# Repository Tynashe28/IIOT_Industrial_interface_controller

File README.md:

# IIOT_Industrial_interface_controller

## Introduction

Remote monitoring and controlling systems are designed to collect data about the operations of any given unit or transmit information to the unit to transform its behavior via the cloud. You benefit from leveraging the Industrial Internet of Things (IIoT). OEMs, end-users and systems integrators have already seen the benefits of implementing a remote monitoring system that lead to increased productivity, reduced production costs and enhanced user experience.

Drakula is an Industrial Internet of Things gateway controller which seeks to connect manufacturing processes to the internet with zero effort and unleash the usefulness and power of technology in this field at zero cost. This controller makes it easy for industries to leverage trending and growing technologies like machine learning, IoT, blockchain, web backend services into their day to day operations. The beauty about Drakula is that it integrates on top of existing architectures and virtually no change can be made to existing setups to accommodate it.  

### Core Values
•	Zero Effort\
•	Zero Cost\
•	Interactive\
•	Value Addition

## How it works

From a high level, the Drakula connects to the plant process and it accesses field parameters about a manufacturing process. It can also be granted privileges to write data to alter the behavior of processes within the plant. Drakula relays this information to a cloud platform via an API where data analytics can also be done.

The ability of this controller to access field parameters and make them accessible over the web opens vast opportunities for manufacturing processes.

•	Information can be relayed to mobile phones, desktop or smart watches.\
•	Interacting with manufacturing processes just becomes easy through our day to day devices.\
•	Implementing sophisticated algorithms which can never be done on PLCs’ in the cloud to improve processes.\
•	Ability to build intuitive and interactive SCADA dashboards which can never be offered by PLCs\

### Example Use Case
Let’s take a practical example of defects after “beer” filling 😃. We can make use of the real time number defects of the filler to come up with the REAL-TIME STATE OF THE MACHINE. We can also produce predictions of the number of defects after some time “x” which can open doors to generate a predictive maintenance schedule for the machine.

## Motivation in Building This Product
•	All most every software and hardware used in industry is highly proprietary to the company that provides that piece of hardware or software. These services come at a hefty amount which leaves us with no room to be innovative with their products as most companies cannot afford. Building a product for less than USD50 to counter this problem should be enough to motivate engineers to start get their hands dirty with these technologies.

•	A PLC is very excellent at the job it was made for. Problems start when you try to perform computations which require more memory or power from the system like training a Machine Learning model. It even gets more complicated than rocket science when you try to perform a simple HTTP request to the internet from a PLC. One of the core values of Drakula is Zero Effort, you don’t have to worry about the low-level implementations of establishing internet connection. Offering this abstraction layer makes engineers focus more on the task to be achieved rather than implementation details.

•	The way reports are generated in industry today is just primitive, data is organized either at end of a shift or day, meaning we don’t get to visualize real-time plant performances. Manufacturing should be also powered by Interactive and Real-time dashboards.

•	A lot of technologies are being developed over the Internet which can be harnessed in operations and processes to increase manufacturing efficiencies and business profitability

## Considerations made into the design

•	Interoperable – Drakula is compatible with almost every industrial setup. It runs in parallel with existing architectures. Taking advantage that every industrial PLC has a communication channel which can be used as desired with no restriction, forms the point of connectivity for the devices.

•	Robust – Controller components to handle high temperatures, voltage fluctuations, electromagnetic interference and induction.

•	Reliability – Additional components to a system has a consequence of reducing the overall reliability of a process. This controller has been designed in a way that it runs in parallel with the overall plant process in a bid to make the controller have zero effect on the plant process in case of a failure. 

•	Hardware Abstraction – Developers implementing this board should have easy ability to integrate this controller. This is made possible by providing ready-to-use drivers which do all low-level heavy lifting.

•	Security & Industrial Standards – The security of a system is as good as its weakest point. This controller aims to keep the integrity of the data that it is processing. Every web request is done via Web-Sockets over HTTPS. Every component used on the controller is accredited to be industrial grade.

•	Overall System Efficiency – Drakula’s main CPU is a high-performance processor which runs a real-time operating system which manages all tasks and this makes sure the system is seamless and operates without any lag.

•	Maintainability – Ability of controller to connect to Wi-Fi access points gives it the ability to be maintained over the air, incase of software updates and troubleshooting. Incase of a hardware fault, the device can be disconnected from the system without affecting the main production processes.

•	Cost – The total cost of producing 1 controller excluding Labour and Tooling is capped at maximum of USD50.00 (PCB Manufacturing, Components and Assembly).

## Why Implement Drakula

### Improve Productivity
Overall Equipment Effectiveness, or OEE, is a productivity measurement that combines downtime, production rate and quality. OEE has long been the gold standard for increasing productivity, but the Industrial Internet of Things has made OEE much more affordable and easier to implement than ever before. 

### Information at Your Fingertips
Line operators, maintenance crews and production supervisors all have a significant impact on the productivity of the manufacturing lines. Without information readily available, it is more difficult to address the highest priority production issues within a timely manner.

### Data Reliability
It’s very common to see people using clipboards to copy data from gauges, operator interface screens or field sensors. Automated data collection is more efficient, more reliable and more consistent than manual data collection. The IIoT can provide seamless data flow starting at the device level and pushing the data directly to mobile devices, enterprise level software or other reporting systems.

### Reduce Downtime
Emails, push notifications and text alerts can provide immediate downtime alerts allowing you to address the issue as quickly as possible.  Root cause analysis allows you to diagnose the specific cause of a downtime event, and downtime analytics allow you to evaluate the true cost of each type of failure.  A remote monitoring solution is an easy and cost-effective way to incorporate all of these techniques to increase the reliability of your equipment.

### Predictive Maintenance
Predictive maintenance techniques can be used to monitor and analyze vibration, motor current, or temperature patterns and identify potential problems before they cause a shutdown. This can also reduce maintenance costs because maintenance can be performed when it is actually needed rather than simply scheduled.

### Intuitive Dashboards
Your car’s dashboard can tell you the remaining oil life, miles to empty, temperature, and more. Manufacturing lines need much more maintenance than a car, but required maintenance is usually not available from the equipment. User friendly dashboards on mobile and desktop apps also provide quick and easy way to visualize the whole plant.

## General System Architecture

### Main-Features
•	Supports all Ethernet communications (Modbus, Profinet, TCP etc.)\
•	Supports Modbus over RS-485\
•	Wi-Fi connectivity (Supports WebSocket connection)\
•	Bi-Directional Communication\
•	Asynchronous and Non-Blocking routines\
•	3 logical Processing Cores

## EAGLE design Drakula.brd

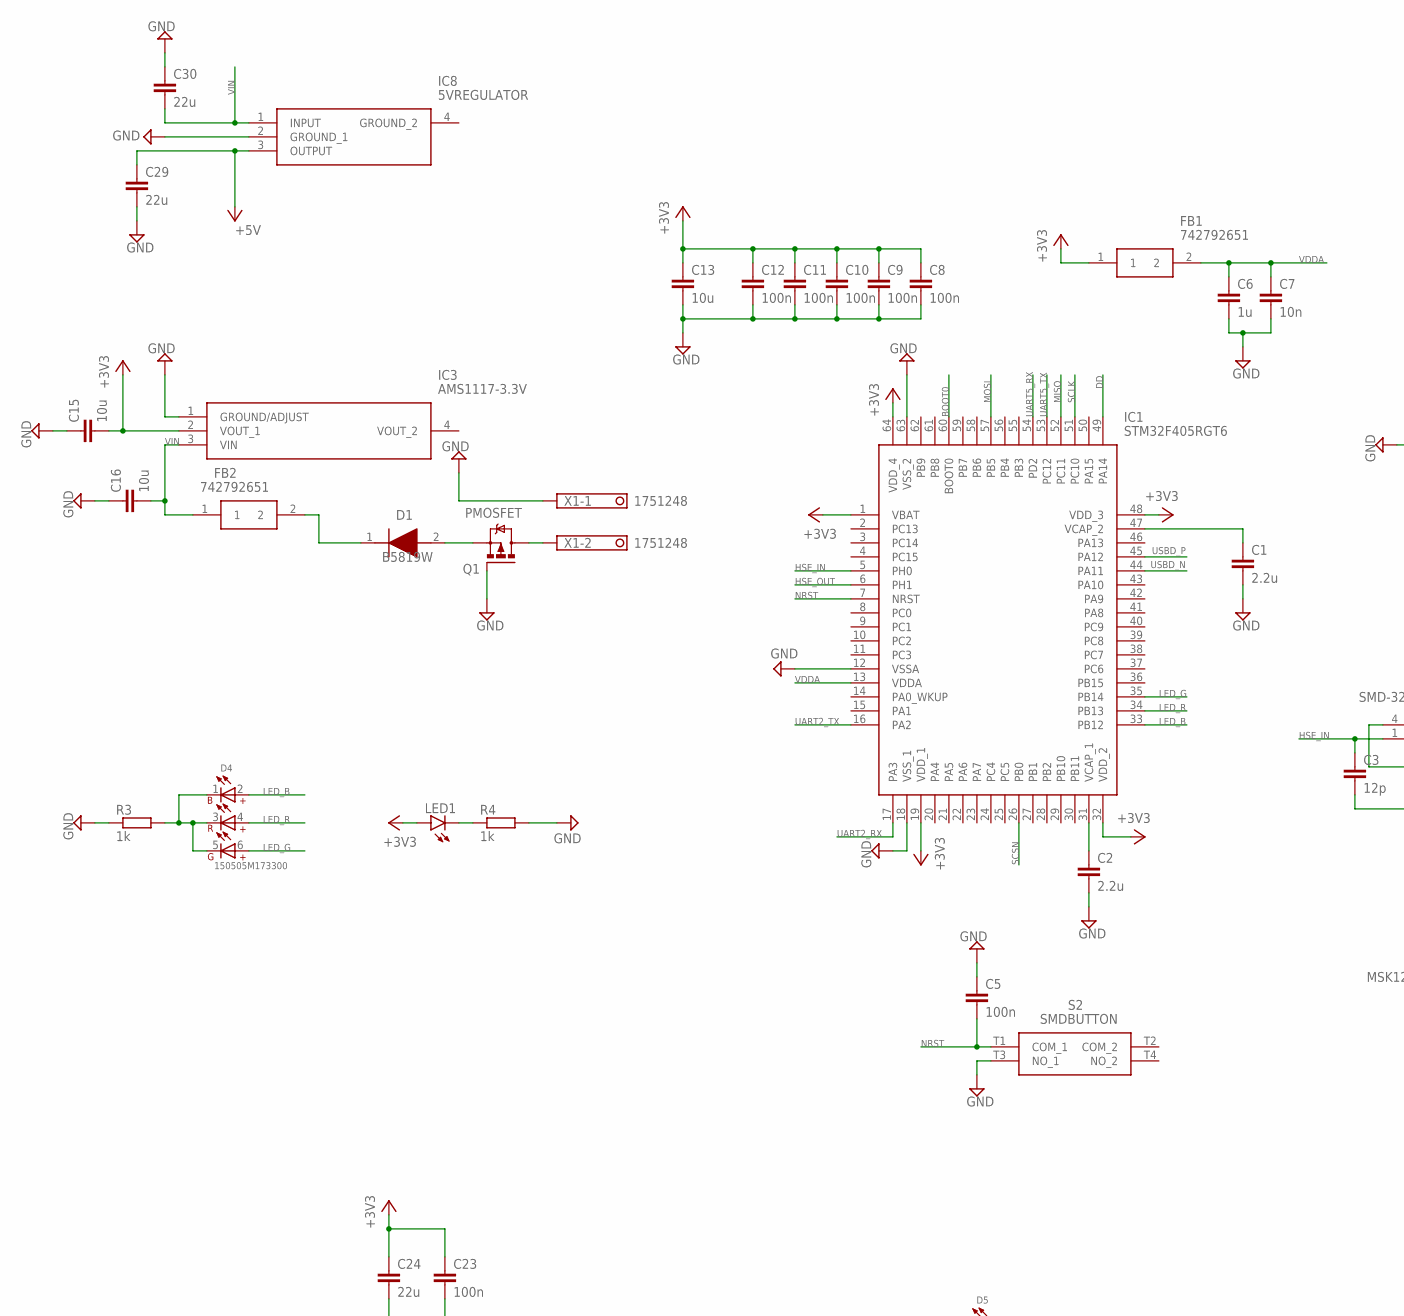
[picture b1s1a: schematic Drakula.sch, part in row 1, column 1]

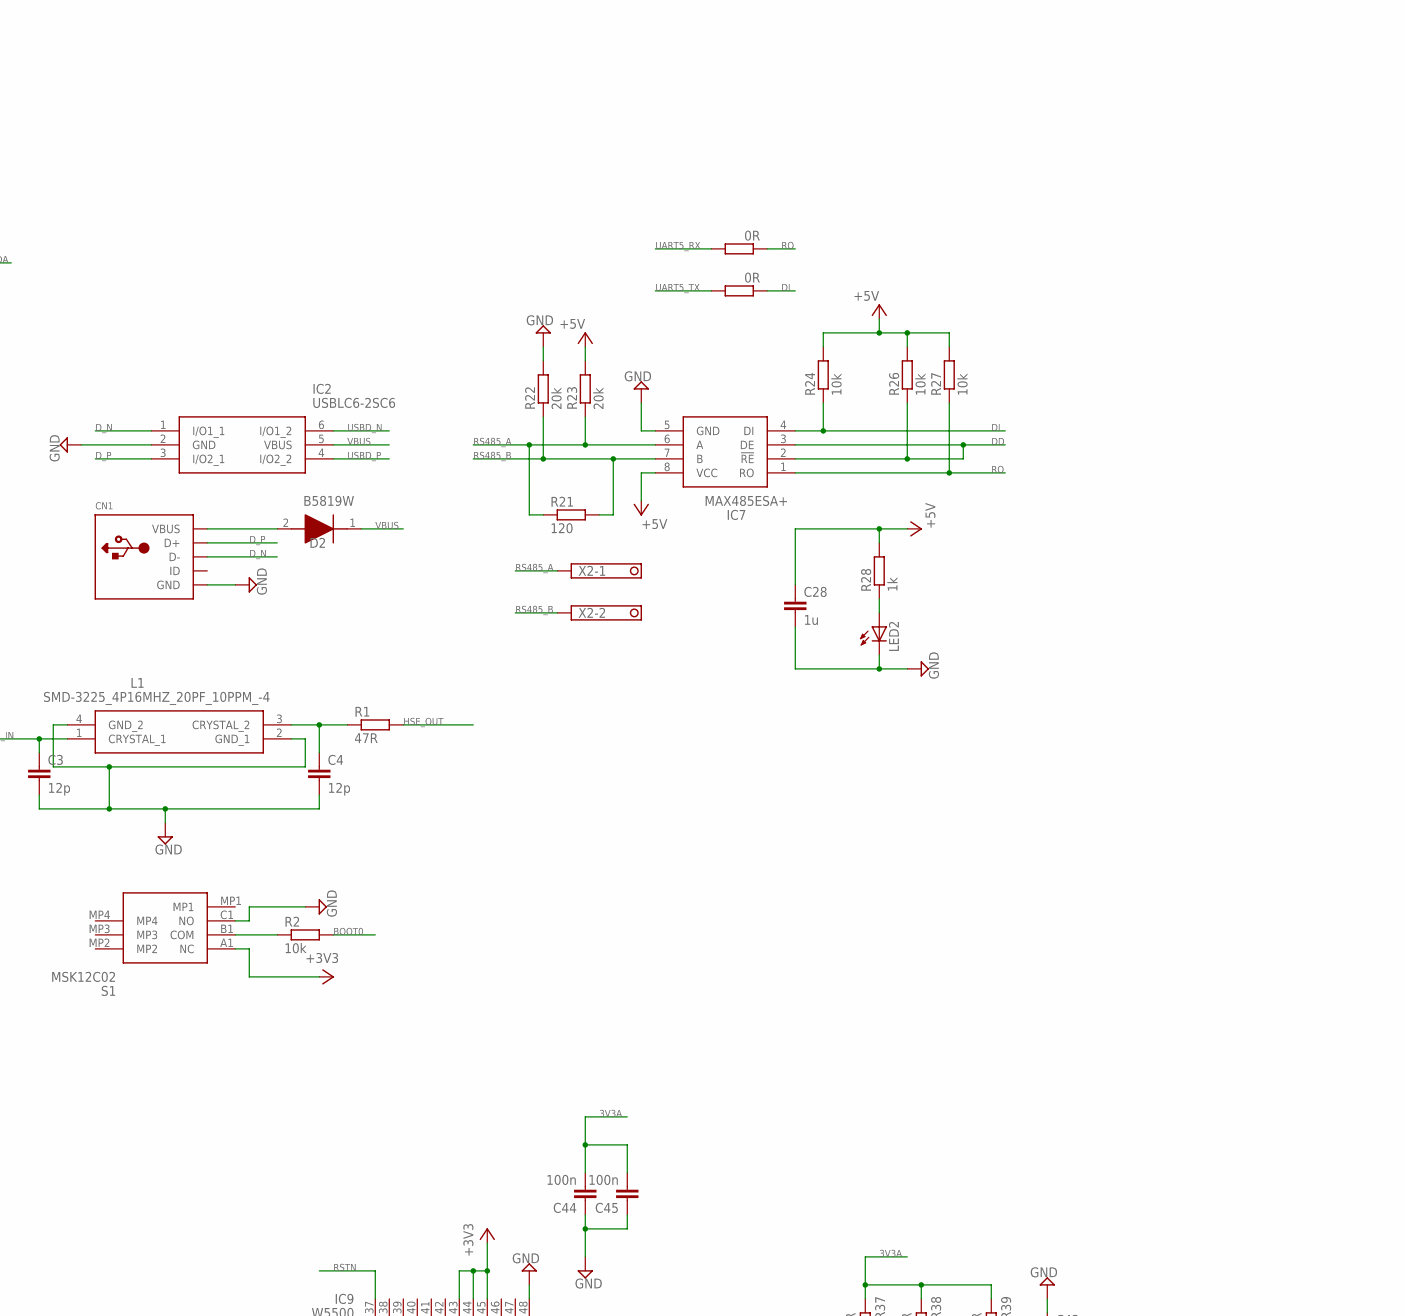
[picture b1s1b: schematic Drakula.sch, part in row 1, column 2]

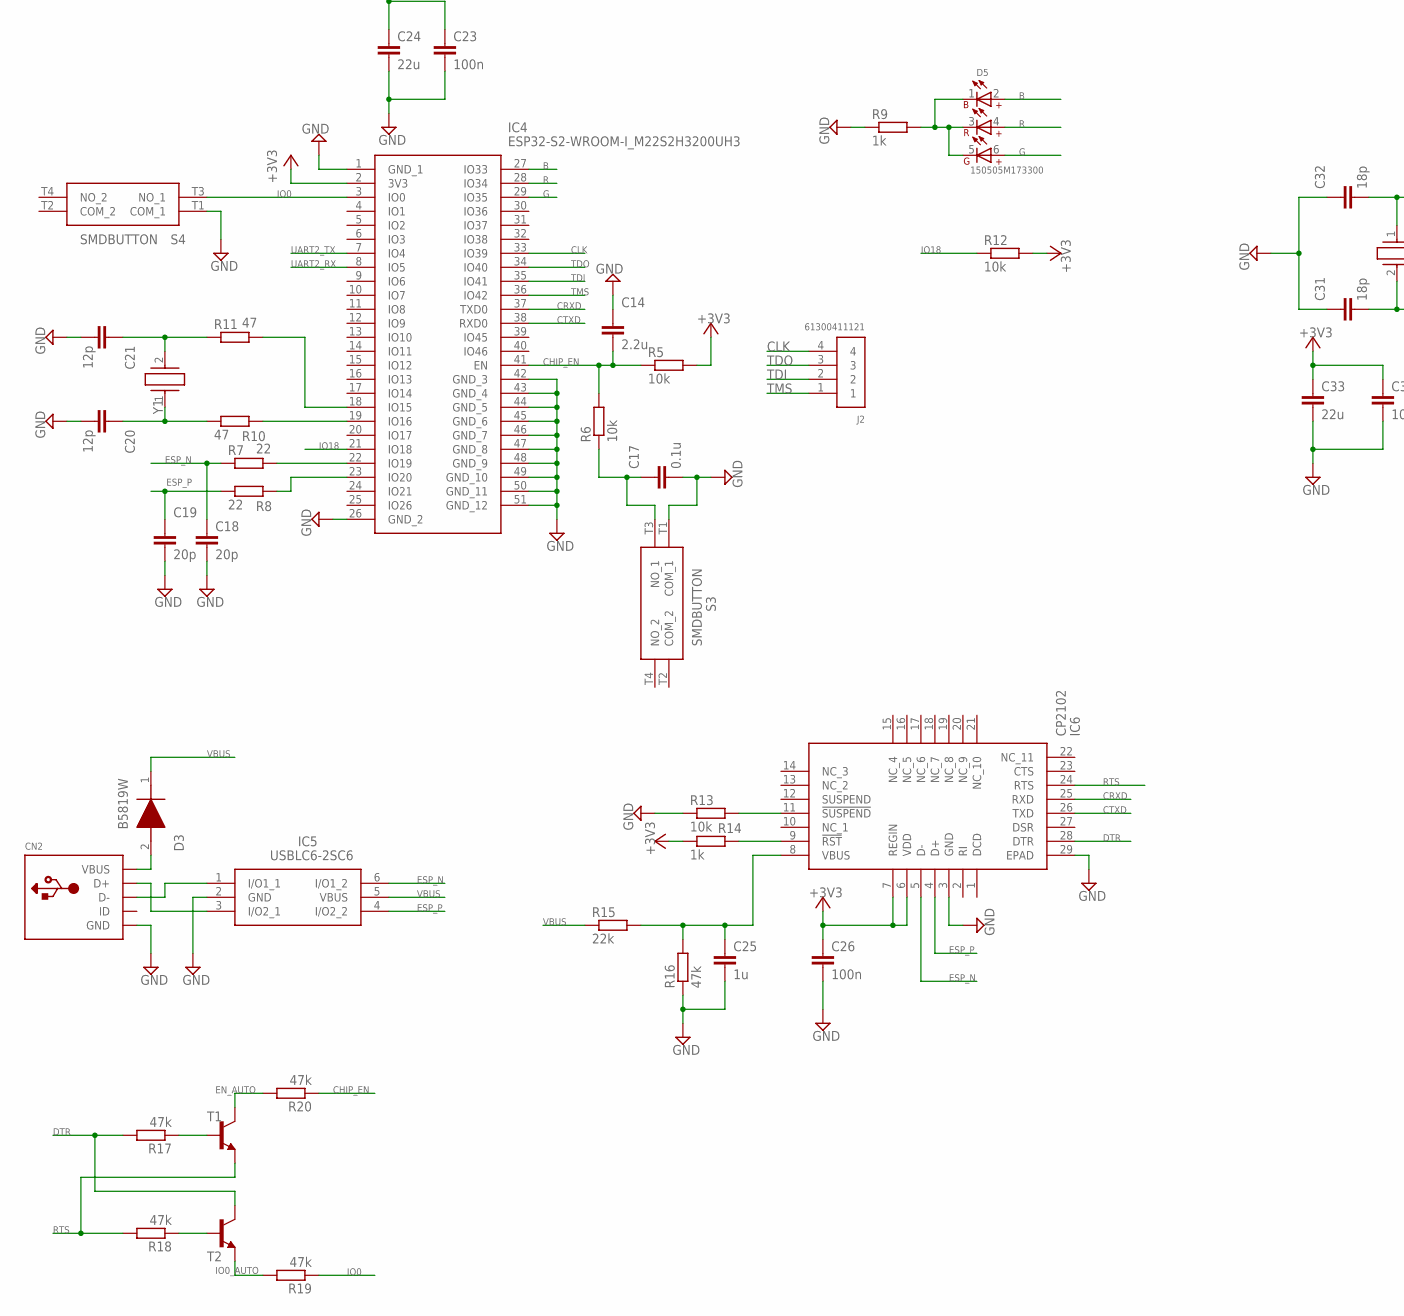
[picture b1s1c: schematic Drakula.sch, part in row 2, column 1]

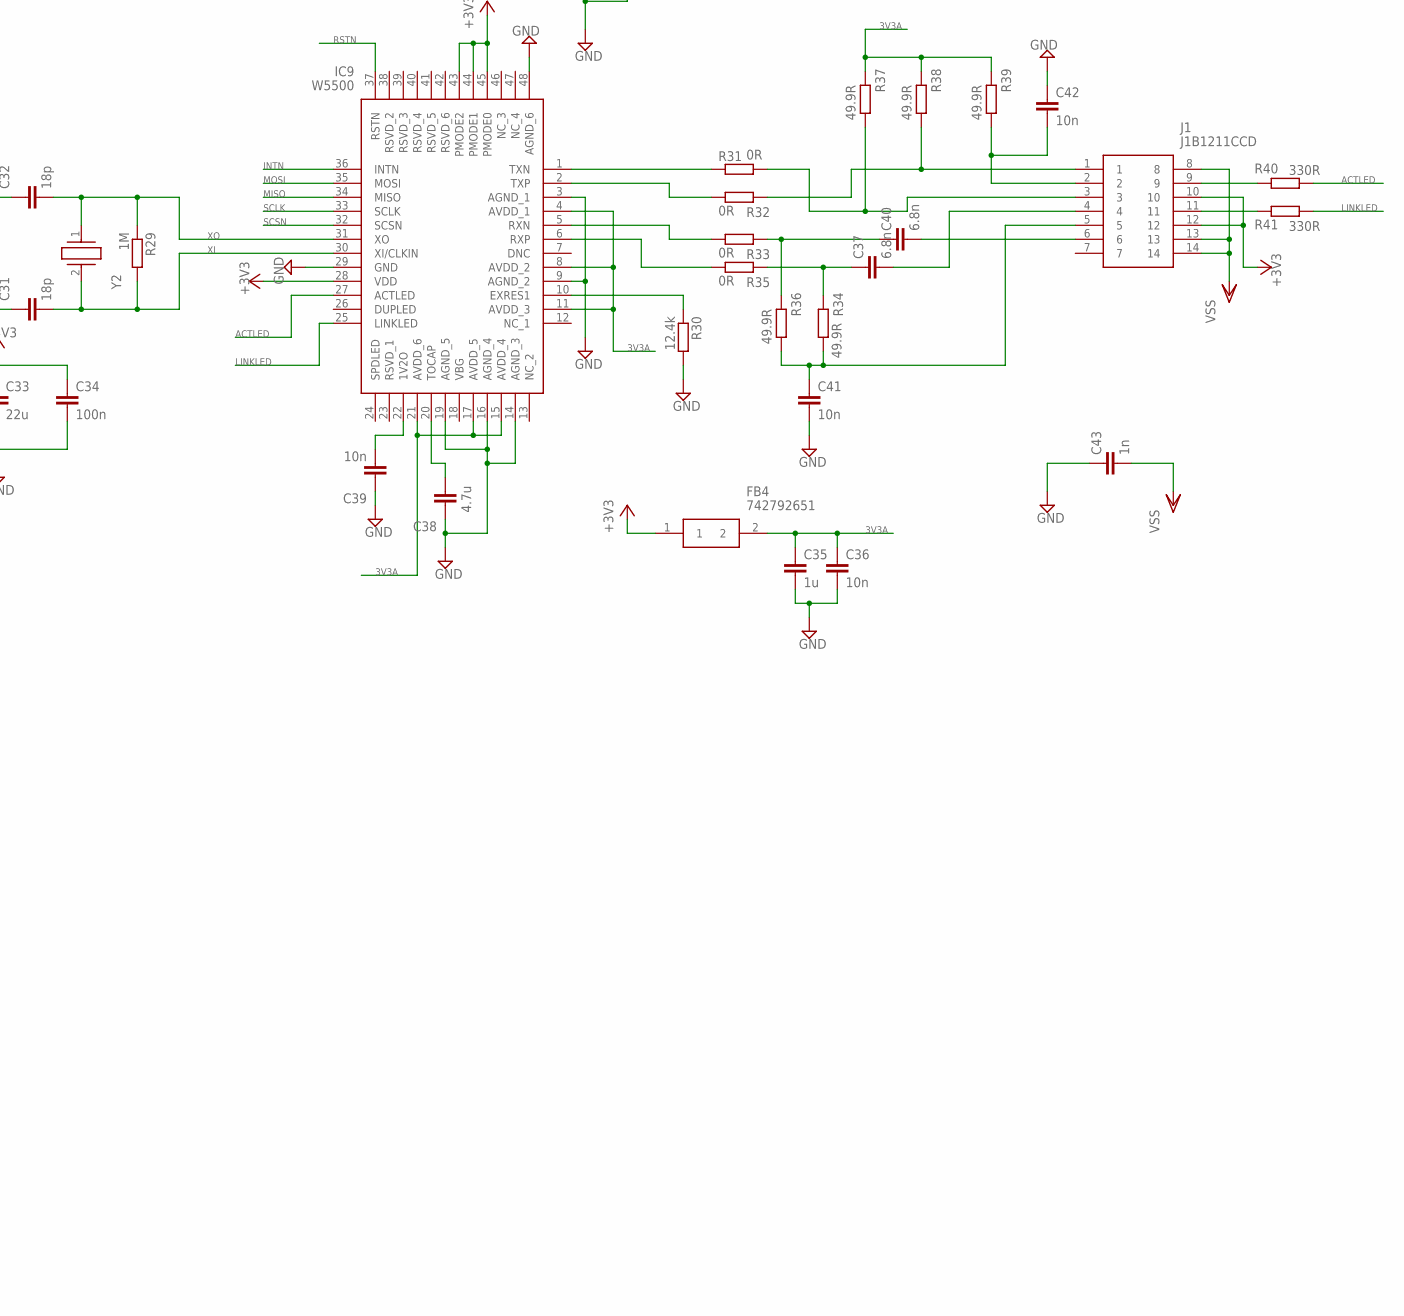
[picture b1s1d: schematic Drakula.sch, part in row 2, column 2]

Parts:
C1, C2, C14: 2.2u; C0603
C3, C4, C20, C21: 12p; C0603
C5, C8, C9, C10, C11, C12, C23, C26, C44, C45: 100n; C0603
C6, C25, C28, C35: 1u; C0603
C7, C36, C39, C41, C42: 10n; C0603
C13, C15, C16: 10u; C0603
C17: 0.1u; C0603
C18, C19: 20p; C0603
C24: 22u; C0603
C29, C30, C33: 22u; C0805
C31, C32: 18p; C0603
C34: 100n; C0805
C37, C40: 6.8n; C0603
C38: 4.7u; C0603
C43: 1n; C0603
CN1, CN2: USBMINIB; USB-MINIB
D1, D2, D3: B5819W
D4, D5: 150505M173300; WL-SFTW_5050_PLCC6
FB1, FB2, FB4: 742792651; BEADC1608X100N
IC1: STM32F405RGT6; STM32F405RTG6
IC2, IC5: USBLC6-2SC6; USBLC6
IC3: AMS1117-3.3V; SOT229P700X180-4N
IC4: ESP32-S2-WROOM-I_M22S2H3200UH3; ESP32S2
IC6: CP2102
IC7: MAX485ESA+; MAX485
IC8: 5VREGULATOR; SOT23-5V
IC9: W5500
J1: J1B1211CCD; RJ45
J2: 61300411121
L1: SMD-3225_4P16MHZ_20PF_10PPM_-4; SMD3225_4P16MHZ20PF10PPM4085
LED1, LED2: LEDCHIPLED_0603; CHIPLED_0603
Q1: PMOSFET; SOT23
R1: 47R; R0603
R2, R5, R6, R12, R24, R26, R27: 10k; R0603
R3, R4, R9, R14: 1k; R0805
R7, R8: 22; R0603
R10, R11: 47; R0603
R13: 10k; R0805
R15: 22k; R0805
R16, R17, R18, R19, R20: 47k; R0805
R21: 120; R0603
R22, R23: 20k; R0603
R28: 1k; R0603
R29: 1M; R0603
R30: 12.4k; R0603
R31, R32, R33, R35, R42, R43: 0R; R0603
R34, R36, R37, R38, R39: 49.9R; R0603
R40, R41: 330R; R0603
S1: MSK12C02
S2, S3, S4: SMDBUTTON
T1, T2: -NPN-SOT23-EBC; SOT23-EBC
X1, X2: 1751248
Y1: FC-135R_32.7680KA-A0; FC135R
Y2: ABM3-25.000MHZ-B2-T; ABM325000MHZB2T

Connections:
3V3A: C35.1, C36.1, C44.2, C45.2, FB4.2, IC9.4 (AVDD_1), IC9.8 (AVDD_2), IC9.11 (AVDD_3), IC9.15 (AVDD_4), IC9.17 (AVDD_5), IC9.21 (AVDD_6), R37.2, R38.2, R39.2
+3V3: C8.1, C9.1, C10.1, C11.1, C12.1, C13.1, C15.2, C23.1, C24.1, C26.1, C33.1, C34.1, FB1.1, FB4.1, IC1.1 (VBAT), IC1.19 (VDD_1), IC1.32 (VDD_2), IC1.48 (VDD_3), IC1.64 (VDD_4), IC3.2 (VOUT_1), IC4.2 (3V3), IC6.6 (VDD), IC6.7 (REGIN), IC9.28 (VDD), IC9.43 (PMODE2), IC9.44 (PMODE1), IC9.45 (PMODE0), J1.10, J1.12, LED1.A, R5.2, R12.2, R14.1, S1.A1 (NC)
+5V: C28.1, C29.1, IC7.8 (VCC), IC8.3 (OUTPUT), R23.2, R24.2, R26.2, R27.2, R28.2
ACTLED: IC9.27 (ACTLED), R40.1
B: D5.2 (B+), IC4.27 (IO33)
BOOT0: IC1.60 (BOOT0), R2.2
CHIP_EN: C14.2, IC4.41 (EN), R5.1, R6.2, R20.1
CLK: IC4.33 (IO39), J2.4
CRXD: IC4.37 (TXD0), IC6.25 (RXD)
CTXD: IC4.38 (RXD0), IC6.26 (TXD)
DD: IC1.49 (PA14), IC7.2 (!RE), IC7.3 (DE), R26.1
DI: IC7.4 (DI), R24.1, R43.1
DTR: IC6.28 (DTR), R17.2, T2.C
D_N: CN1.D-, IC2.1 (I/O1_1)
D_P: CN1.D+, IC2.3 (I/O2_1)
EN_AUTO: R20.2, T1.C
ESP_N: C18.1, IC5.6 (I/O1_2), IC6.5 (D-), R7.1
ESP_P: C19.1, IC5.4 (I/O2_2), IC6.4 (D+), R8.1
G: D5.6 (G+), IC4.29 (IO35)
GND: C1.2, C2.2, C3.2, C4.2, C5.1, C6.2, C7.2, C8.2, C9.2, C10.2, C11.2, C12.2, C13.2, C14.1, C15.1, C16.1, C17.2, C18.2, C19.2, C20.2, C21.2, C23.2, C24.2, C25.2, C26.2, C28.2, C29.2, C30.1, C31.1, C32.1, C33.2, C34.2, C35.2, C36.2, C38.1, C39.1, C41.2, C42.1, C43.1, C44.1, C45.1, CN1.GND, CN2.GND, IC1.12 (VSSA), IC1.18 (VSS_1), IC1.63 (VSS_2), IC2.2 (GND), IC3.1 (GROUND/ADJUST), IC4.1 (GND_1), IC4.26 (GND_2), IC4.42 (GND_3), IC4.43 (GND_4), IC4.44 (GND_5), IC4.45 (GND_6), IC4.46 (GND_7), IC4.47 (GND_8), IC4.48 (GND_9), IC4.49 (GND_10), IC4.50 (GND_11), IC4.51 (GND_12), IC5.2 (GND), IC6.3 (GND), IC6.29 (EPAD), IC7.5 (GND), IC8.2 (GROUND_1), IC9.3 (AGND_1), IC9.9 (AGND_2), IC9.14 (AGND_3), IC9.16 (AGND_4), IC9.19 (AGND_5), IC9.29 (GND), IC9.48 (AGND_6), L1.2 (GND_1), L1.4 (GND_2), LED2.C, Q1.1 (G), R3.1, R4.2, R9.1, R13.1, R16.1, R22.2, R30.2, S1.C1 (NO), S2.T3 (NO_1), S3.T1 (COM_1), S4.T1 (COM_1), X1.1
HSE_IN: C3.1, IC1.5 (PH0), L1.1 (CRYSTAL_1)
HSE_OUT: IC1.6 (PH1), R1.2
INTN: IC9.36 (INTN)
IO0: IC4.3 (IO0), R19.1, S4.T3 (NO_1)
IO0_AUTO: R19.2, T2.E
IO18: IC4.21 (IO18), R12.1
LED_B: D4.2 (B+), IC1.33 (PB12)
LED_G: D4.6 (G+), IC1.35 (PB14)
LED_R: D4.4 (R+), IC1.34 (PB13)
LINKLED: IC9.25 (LINKLED), R41.1
MISO: IC1.52 (PC11), IC9.34 (MISO)
MOSI: IC1.57 (PB5), IC9.35 (MOSI)
unnamed: Q1.3 (D), X1.2
unnamed: D1.1 (K), FB2.2
unnamed: D1.2 (A), Q1.2 (S)
unnamed: D4.1 (B-), D4.3 (R-), D4.5 (G-), R3.2
unnamed: R2.1, S1.B1 (COM)
unnamed: LED1.C, R4.1
unnamed: C17.1, R6.1, S3.T3 (NO_1)
unnamed: CN2.D-, IC5.1 (I/O1_1)
unnamed: CN2.D+, IC5.3 (I/O2_1)
unnamed: CN2.VBUS, D3.2 (A)
unnamed: CN1.VBUS, D2.2 (A)
unnamed: IC4.22 (IO19), R7.2
unnamed: IC4.23 (IO20), R8.2
unnamed: IC4.18 (IO15), R11.2
unnamed: C2.1, IC1.31 (VCAP_1)
unnamed: C1.1, IC1.47 (VCAP_2)
unnamed: IC4.19 (IO16), R10.2
unnamed: C4.1, L1.3 (CRYSTAL_2), R1.1
unnamed: C20.1, R10.1, Y1.1
unnamed: C21.1, R11.1, Y1.2
unnamed: C25.1, IC6.8 (VBUS), R15.2, R16.2
unnamed: IC6.11 (!SUSPEND), R13.2
unnamed: IC6.9 (!RST), R14.2
unnamed: D5.1 (B-), D5.3 (R-), D5.5 (G-), R9.2
unnamed: R17.1, T1.B
unnamed: R18.1, T2.B
unnamed: C39.2, IC9.22 (1V2O)
unnamed: C38.2, IC9.20 (TOCAP)
unnamed: LED2.A, R28.1
unnamed: IC9.10 (EXRES1), R30.1
unnamed: IC9.1 (TXN), R31.1
unnamed: IC9.2 (TXP), R32.1
unnamed: IC9.5 (RXN), R33.1
unnamed: IC9.6 (RXP), R35.1
unnamed: J1.1, R32.2, R38.1
unnamed: J1.3, R31.2, R37.1
unnamed: C40.2, J1.6
unnamed: C37.2, J1.4
unnamed: C37.1, R34.2, R35.2
unnamed: C40.1, R33.2, R36.2
unnamed: C41.1, J1.5, R34.1, R36.1
unnamed: J1.9, R40.2
unnamed: C42.2, J1.2, R39.1
unnamed: J1.11, R41.2
NRST: C5.2, IC1.7 (NRST), S2.T1 (COM_1)
R: D5.4 (R+), IC4.28 (IO34)
RO: IC7.1 (RO), R27.1, R42.1
RS485_A: IC7.6 (A), R21.1, R23.1, X2.1
RS485_B: IC7.7 (B), R21.2, R22.1, X2.2
RSTN: IC9.37 (RSTN)
RTS: IC6.24 (RTS), R18.2, T1.E
SCLK: IC1.51 (PC10), IC9.33 (SCLK)
SCSN: IC1.26 (PB0), IC9.32 (SCSN)
TDI: IC4.35 (IO41), J2.2
TDO: IC4.34 (IO40), J2.3
TMS: IC4.36 (IO42), J2.1
UART2_RX: IC1.17 (PA3), IC4.8 (IO5)
UART2_TX: IC1.16 (PA2), IC4.7 (IO4)
UART5_RX: IC1.54 (PD2), R42.2
UART5_TX: IC1.53 (PC12), R43.2
USBD_N: IC1.44 (PA11), IC2.6 (I/O1_2)
USBD_P: IC1.45 (PA12), IC2.4 (I/O2_2)
VBUS: D2.1 (K), D3.1 (K), IC2.5 (VBUS), IC5.5 (VBUS), R15.1
VDDA: C6.1, C7.1, FB1.2, IC1.13 (VDDA)
VIN: C16.2, C30.2, FB2.1, IC3.3 (VIN), IC8.1 (INPUT)
VSS: C43.2, J1.8, J1.13, J1.14
XI: C31.2, IC9.30 (XI/CLKIN), R29.2, Y2.2
XO: C32.2, IC9.31 (XO), R29.1, Y2.1

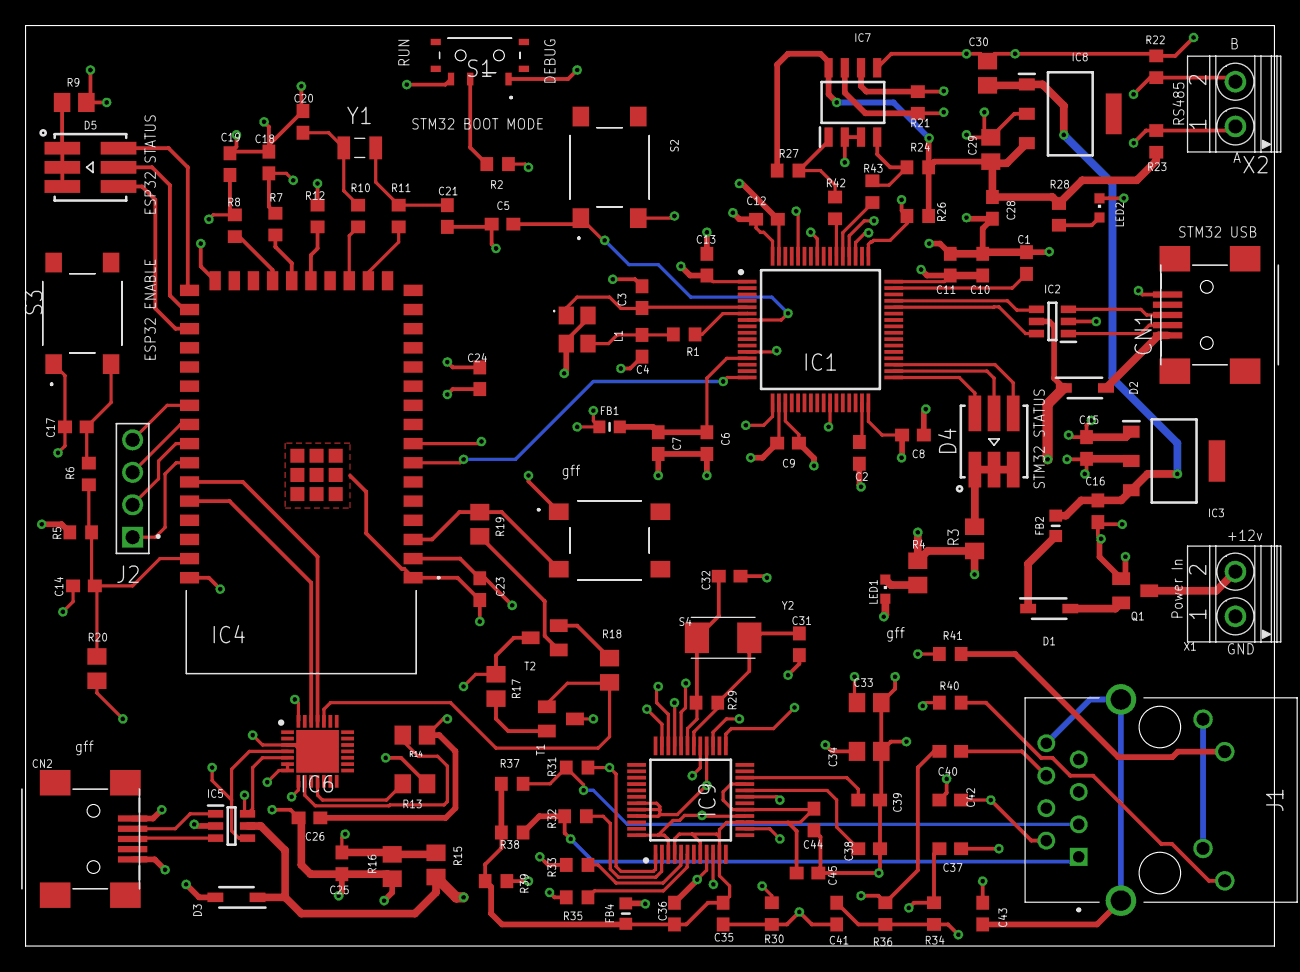
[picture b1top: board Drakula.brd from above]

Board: 4 copper layers, 97.8 x 72.1 mm, 120 parts (0 on the bottom side), 98 nets.

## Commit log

2022-08-02 init on schematics
2022-08-02 added max485
2022-08-03 done schematic
2022-09-19 added doc with product description
2022-09-19 added images

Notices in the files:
parts and their libraries:
Wurth_LEDs_WL-SFTW: Copyright: Würth Elektronik
